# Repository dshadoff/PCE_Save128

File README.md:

# PCE_Save128
FPGA Implementation of reverse-engineered Memory Base 128/Save-Kun device

This project is designed to reimplement the features of the PC Engine's
Save-kun or Memory Base 128 devices in a modern FPGA device rather than a
customized ASIC.

SPI FeRAM is also in use, with the benefit of being non-volatile.

A MachXO2 FPGA was used due to its relatively low cost, internal Flash
reprogrammability, and simple power supply requirements. Additionally, the
TinyFPGA Ax-series of hobbyist boards helped to facilitate the prototyping
process.

The firmware is coded in Veriog using Lattice's Diamond software; the on-chip
SPI interface was not used; instead, a very limited set of SPI commands is
custom-written for communication with the FeRAM chip.

This repository includes the following folders:

EAGLE :
- these files are the project deisgn files for the PC Board in EAGLE
- Additional information for SMD assembly by JLCPCB are also included, files bom.csv and assembly.csv

firmware:
- This is the project folder for Lattice Diamond, using a MachXO2 FPGA of part number "LCMXO2-1200HC-4SG32C" - as found in the TinyFPGA AX2 board (which is used as a sub-assembly)
- key files are:
 - Save128.v - main verilog file
 - top.v - the top-level module
 - Save128.lpf - pin assignment settings file
 - testbench.v - a testbench which assists in visualizing various scenarios in simulation

release:
- Includes both an SRAM image (.bit) and Flash image (.jed).
- Filename base ends in "yyyymmdd" date format.

TODOs:
------
- shrink PC board
- possibly integrate the FPGA directly onto the main PC board
- design an enclosure of some sort

This is prototype software, and as such has been minimally tested.
Use at your own risk.

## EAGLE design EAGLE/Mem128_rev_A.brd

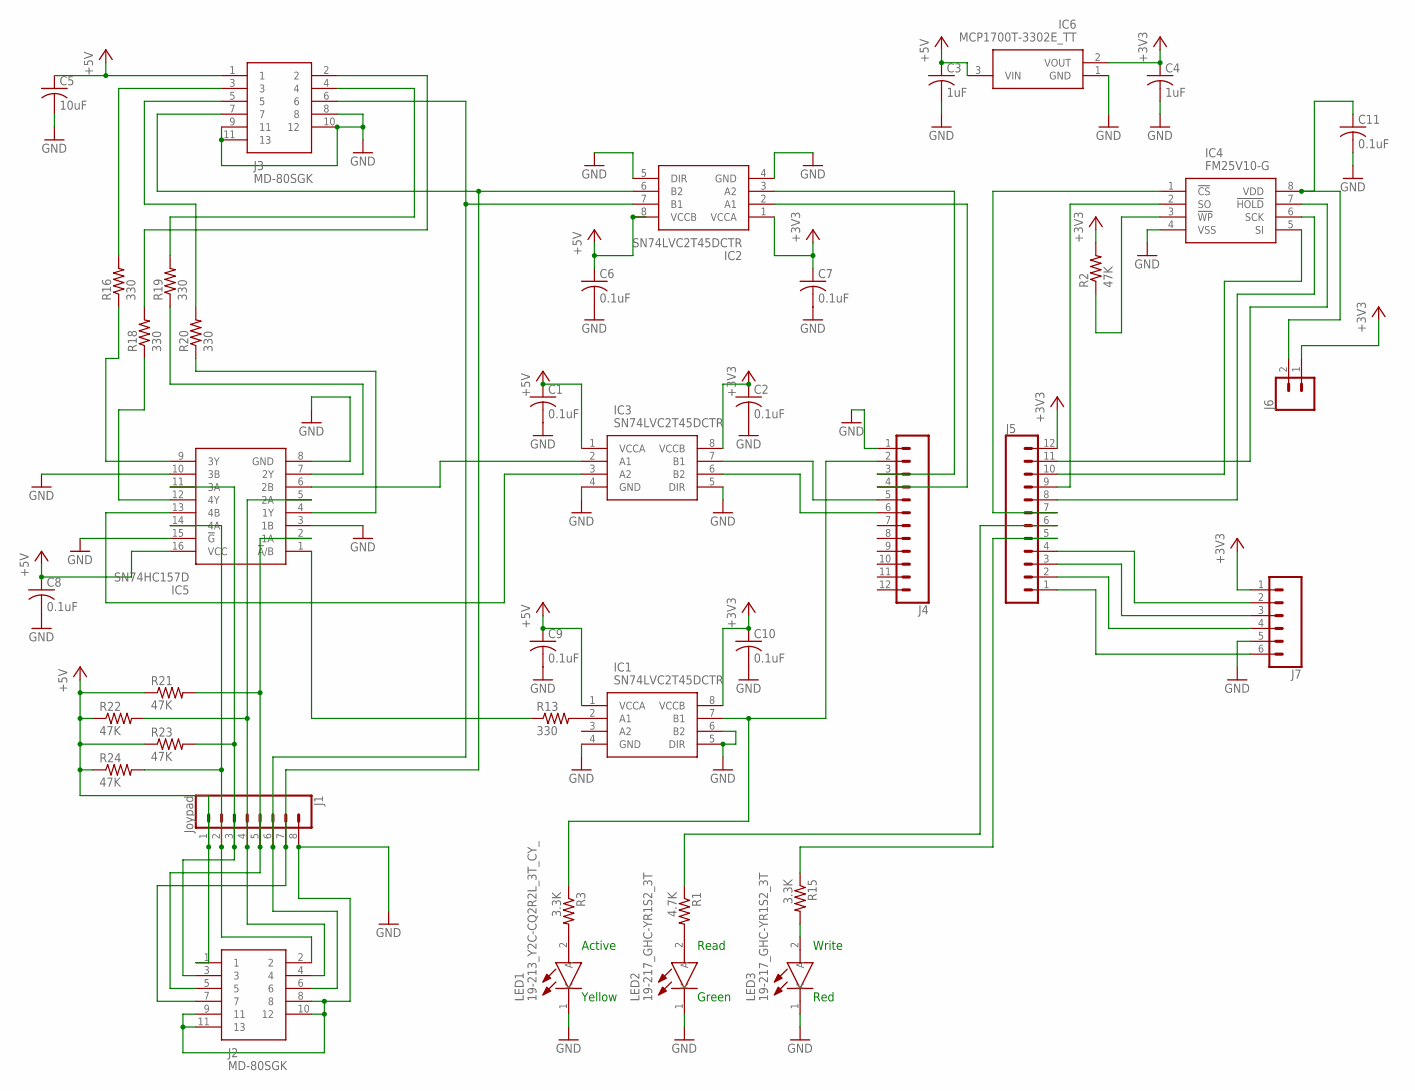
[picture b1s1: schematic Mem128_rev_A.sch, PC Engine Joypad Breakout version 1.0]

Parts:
C1, C2, C6, C7, C8, C9, C10, C11: 0.1uF; C0603
C3, C4: 1uF; C0603
C5: 10uF; C0805
IC1, IC2, IC3: SN74LVC2T45DCTR; SOP65P400X130-8N
IC4: FM25V10-G; SOIC127P602X173-8N
IC5: SN74HC157D; SOIC127P600X175-16N
IC6: MCP1700T-3302E_TT; SOT95P237X112-3N
J1: Joypad; 1X08
J2, J3: MD-80SGK; MD80SGK
J4, J5: CONN_12; 1X12
J6: CONN_02; 1X02
J7: CONN_06NO_SILK_FEMALE_PTH; 1X06_NO_SILK
LED1: 19-213_Y2C-CQ2R2L_3T_CY_; LEDC1608X60N
LED2: 19-217_GHC-YR1S2_3T; LEDC1608X50N
LED3: 19-217_GHC-YR1S2_3T; LEDC1608X50N; MANUFACTURER_PART_NUMBER KT-0603R
R1: 4.7K; R0603
R2, R21, R22, R23, R24: 47K; R0603
R3, R15: 3.3K; R0603
R13, R16, R18, R19, R20: 330; R0603

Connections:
+3V3: C2.1, C4.1, C7.1, C10.1, IC1.8 (VCCB), IC2.1 (VCCA), IC3.8 (VCCB), IC6.2 (VOUT), J5.12, J6.1, J7.1, R2.2
+5V: C1.1, C3.1, C5.1, C6.1, C8.1, C9.1, IC1.1 (VCCA), IC2.8 (VCCB), IC3.1 (VCCA), IC5.16 (VCC), IC6.3 (VIN), J1.1, J2.1, J3.1, R21.1, R22.1, R23.1, R24.1
CLR: IC2.6 (B2), J1.7, J2.7, J3.7
D6: J5.5, R15.1
D10: J5.6, R1.1
D11: IC1.7 (B1), J4.2, R3.1
GND: C1.2, C2.2, C3.2, C4.2, C5.2, C6.2, C7.2, C8.2, C9.2, C10.2, C11.2, IC1.4 (GND), IC1.5 (DIR), IC1.6 (B2), IC2.4 (GND), IC2.5 (DIR), IC3.4 (GND), IC3.5 (DIR), IC4.4 (VSS), IC5.3 (1B), IC5.8 (GND), IC5.10 (3B), IC5.15 (!G), IC6.1 (GND), J1.8, J2.8, J2.9 (11), J2.10 (12), J2.11 (13), J3.8, J3.9 (11), J3.10 (12), J3.11 (13), J4.1, J7.5, LED1.1 (K), LED2.1 (K), LED3.1 (K)
unnamed: LED2.2 (A), R1.2
unnamed: IC5.11 (3A), J1.3, J2.3, R23.2
unnamed: IC5.14 (4A), J1.2, J2.2, R24.2
unnamed: LED1.2 (A), R3.2
unnamed: IC4.7 (!HOLD), J5.11
unnamed: IC4.6 (SCK), J5.8
unnamed: J3.5, R20.2
unnamed: J3.4, R19.2
unnamed: J3.3, R16.2
unnamed: C11.1, IC4.8 (VDD), J6.2
unnamed: IC5.1 (!A!/B), R13.1
unnamed: IC1.2 (A1), R13.2
unnamed: IC5.5 (2A), J1.4, J2.4, R22.2
unnamed: IC5.9 (3Y), R16.1
unnamed: IC5.2 (1A), J1.5, J2.5, R21.2
unnamed: IC3.2 (A1), IC5.6 (2B)
unnamed: IC5.12 (4Y), R18.1
unnamed: IC5.4 (1Y), R20.1
unnamed: J3.2, R18.2
unnamed: IC5.7 (2Y), R19.1
unnamed: IC4.3 (!WP), R2.1
unnamed: IC4.1 (!CS), J5.7
unnamed: IC4.5 (SI), J5.10
unnamed: IC3.3 (A2), IC5.13 (4B)
unnamed: IC4.2 (SO), J5.9
unnamed: IC2.3 (A2), J4.3
unnamed: IC3.7 (B1), J4.5
unnamed: IC3.6 (B2), J4.6
unnamed: J5.1, J7.6
unnamed: LED3.2 (A), R15.2
unnamed: J5.2, J7.4
unnamed: J5.3, J7.3
unnamed: J5.4, J7.2
RX: IC2.2 (A1), J4.4
SEL: IC2.7 (B1), J1.6, J2.6, J3.6

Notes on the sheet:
Active
Read
Write
Yellow
Green
Red

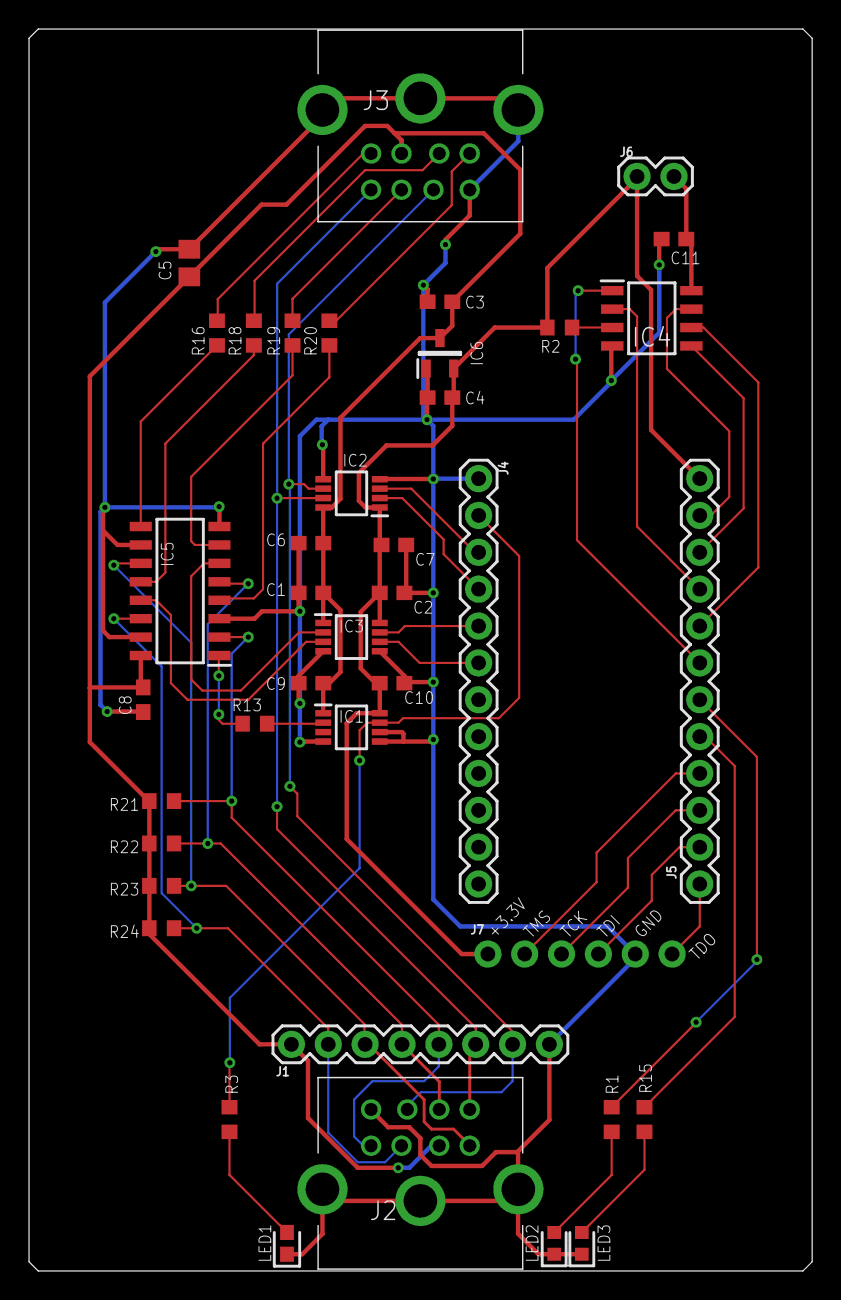
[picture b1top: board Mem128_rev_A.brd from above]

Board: 2 copper layers, 54.0 x 85.6 mm, 40 parts (0 on the bottom side), 42 nets.

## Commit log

2020-07-13 Initialize project
    add gitignore, LICEENSE and README files
2020-07-14 Firmware skeleton project
    Add files necessary to compile a project in Diamond
    This is just a 'blinky' project at the moment
2020-07-16 Minor project tweaks
    - update Diamond version
    - alter speed constraint for project
2020-07-18 Add more project files to ignore
2020-08-18 Add programming subproject (Lattice programmer)
2020-08-18 Program to SRAM
2020-10-13 Implement simple bit-bang SPI
2020-10-18 Get SPI working...sort of
    SPI read function roks for first read; subsequent accesses need to be debugged.
2020-10-18 SPI read working a little bit more
    HOLD functionality still not working properly, but subsequent full SPI transactions now work.
2020-10-25 Test setup and write to FeRAM - working
2021-04-17 Nearly working
2021-04-18 Some fixes diuring simulation
2021-04-18 Tested working but not cleaned up
2021-04-18 Clean up comments/remove commented-out code
2021-04-18 Clean up simulation folders, create release
2021-04-18 Add EAGLE PC Board design files
2021-04-18 Correct a couple of warnings
2021-04-18 Update documentation
2021-04-18 fix formatting
2021-04-24 Correct references within project file

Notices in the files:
EAGLE/Mem128_rev_A.brd:
(C)2020 David Shadoff
parts and their libraries:
SparkFun-Connectors: Licensing: Creative Commons ShareAlike 4.0 International - https://creativecommons.org/licenses/by-sa/4.0
